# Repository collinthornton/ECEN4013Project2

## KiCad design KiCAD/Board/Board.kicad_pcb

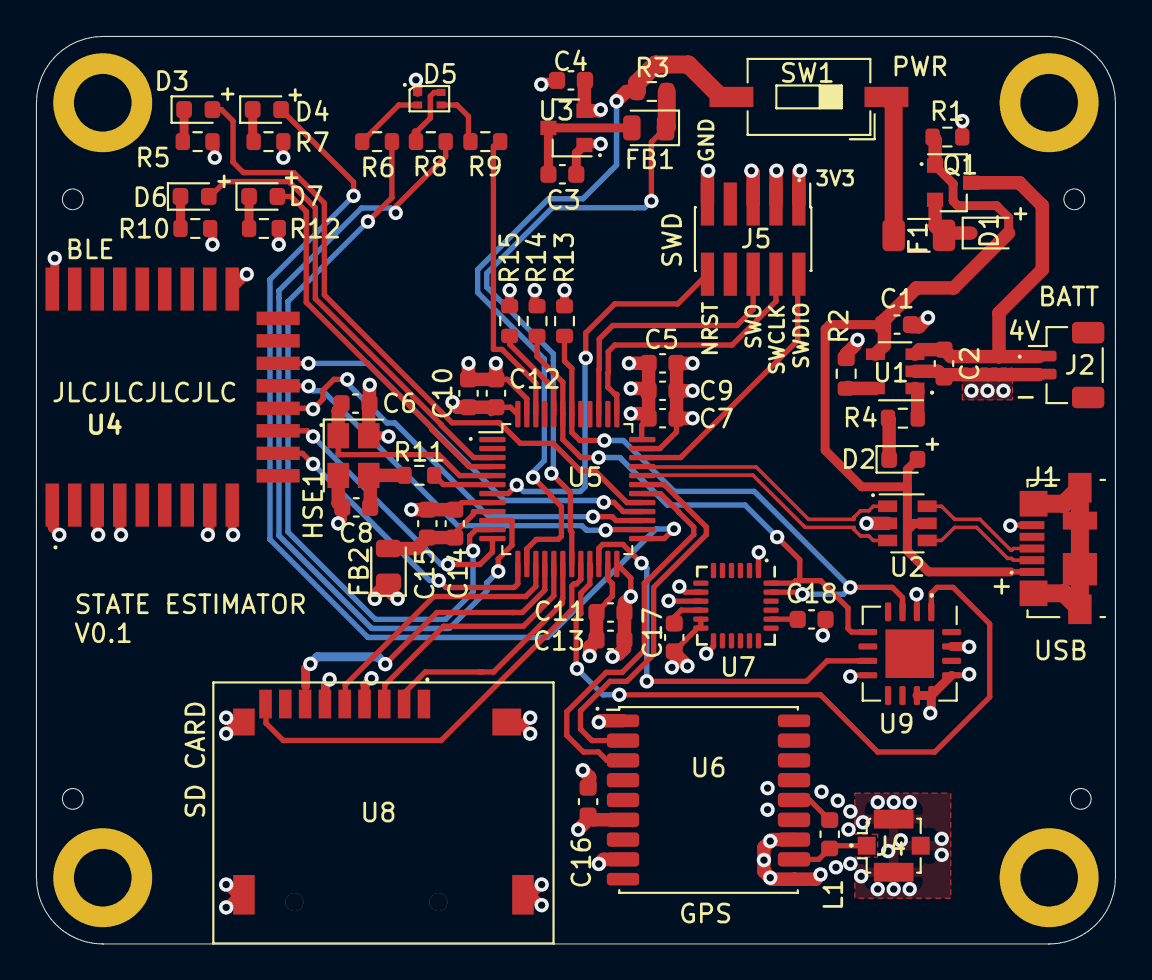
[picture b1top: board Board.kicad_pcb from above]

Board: 4 copper layers, 59.9 x 50.4 mm, 64 parts (0 on the bottom side), 59 nets.

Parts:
C1, C2: 4.7uF; C_0603_1608Metric
C3, C4: 1u; C_0603_1608Metric
C5, C16: 10u; C_0603_1608Metric
C6, C8: 14pF; C_0603_1608Metric
C7, C9, C10, C11, C12, C13, C14: 100n; C_0603_1608Metric
C15: 10n; C_0603_1608Metric
C17: 0.1u; C_0603_1608Metric
C18: 2.2n; C_0603_1608Metric
D1: D_Schottky; D_SOD-323
D2: CHARGE_LED_R; LED_0603_1608Metric
D3: GPS_STATUS; LED_0603_1608Metric
D4: SD_ACT; LED_0603_1608Metric
D5: BATT_STAT; APHF1608LSEEQBDZGKC
D6: USB_ACT; LED_0603_1608Metric
D7: BLE_CON; LED_0603_1608Metric
F1: 500mA; Fuse_1206_3216Metric
FB1, FB2: 100 @ 100 MHz; D_0805_2012Metric
H1, H2, H3, H4: MountingHole_Pad; MountingHole_3.2mm_M3_ISO14580_Pad
HSE1: 24MHz; Crystal_SMD_3225-4Pin_3.2x2.5mm
J1: USB_OTG; USB_Micro-B_Molex_47346-0001
J2: JST_BATT; JST_SH_BM02B-SRSS-TB_1x02-1MP_P1.00mm_Vertical
J4: Conn_Coaxial; U.FL_Molex_MCRF_73412-0110_Vertical
J5: Conn_02x05_Odd_Even; PinHeader_2x05_P1.27mm_Vertical_SMD
L1: 27nH; L_0603_1608Metric
Q1: PWR_PMOS; SOT-23
R1, R15: 10k; R_0603_1608Metric
R2: 5k; R_0603_1608Metric
R3: 0.4; R_0603_1608Metric
R4: 470; R_0603_1608Metric
R5, R7, R10, R12: 10; R_0603_1608Metric
R6: 50; R_0603_1608Metric
R8, R9: 34; R_0603_1608Metric
R11: 220; R_0603_1608Metric
R13, R14: 2k2; R_0603_1608Metric
SW1: ON_OFF; SW_DIP_SPSTx01_Slide_6.7x4.1mm_W8.61mm_P2.54mm_LowProfile
U1: MCP73831-2-OT; SOT-23-5
U2: USBLC6-2SC6; SOT-23-6
U3: ME6211A28M3G-N; SOT-23
U4: DS-32-BLE4.2; DL-32-BLE4.2
U5: STM32L151C8TxA; LQFP-48_7x7mm_P0.5mm
U6: ATGM336H-1N; ublox_MAX
U7: MPU-6050; InvenSense_QFN-24_4x4mm_P0.5mm
U8: Micro_SD_TF-15; MICRO_SD_TF-15
U9: MLX90393; QFN-16-1EP_5x5mm_P0.8mm_EP2.7x2.7mm

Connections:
+3.3VA: C14.1, C15.1, FB2.2, U5.9
+3V3: C4.1, C5.1, C7.1, C9.1, C10.1, C11.1, C12.1, C13.1, C16.1, D5.1, FB2.1, J5.1, R13.1, R14.1, U3.2, U4.8, U5.24, U5.36, U5.48, U6.6, U6.8, U7.8, U7.13, U8.4, U9.2, U9.8, U9.15
+5V: C1.1, D1.2, D2.2, J1.1, Q1.1, R1.1, U1.4, U2.5
BLE_EN: U4.15, U5.28
BLE_INT: U4.14, U5.26
BLE_LED_G: D7.2, U5.4
BLE_STATUS: U4.13, U5.27
BOOT0: R15.1, U5.44
GND: C1.2, C2.2, C3.2, C4.2, C5.2, C6.2, C7.2, C8.2, C9.2, C10.2, C11.2, C12.2, C13.2, C14.2, C15.2, C16.2, C17.2, C18.2, H1.1, H2.1, H3.1, H4.1, HSE1.2, HSE1.4, J1.5, J2.2, J4.2, J5.3, J5.5, J5.9, R1.2, R2.2, R5.2, R7.2, R10.2, R12.2, R15.2, U1.2, U2.2, U3.1, U4.1, U4.3, U4.4, U4.9, U4.18, U4.26, U5.8, U5.23, U5.35, U5.47, U6.1, U6.10, U6.12, U7.1, U7.9, U7.11, U7.12, U8.6, U9.11, U9.12, U9.13
GPS_LED_G: D3.2, U5.29
HSE_IN: C6.1, HSE1.1, U5.5
HSE_OUT: R11.1, U5.6
I2C1_SCL: R13.2, U5.42, U7.23, U9.3
I2C1_SDA: R14.2, U5.43, U7.24, U9.5
MLX_RDY: U5.21, U9.1
MLX_TRIG: U5.22, U9.7
NRST: J5.10, U5.7
unnamed: C3.1, FB1.2, U3.3
unnamed: C8.1, HSE1.3, R11.2
unnamed: C17.1, U7.10
unnamed: C18.1, U7.20
unnamed: D1.1, F1.2, Q1.2
unnamed: D2.1, R4.2
unnamed: D3.1, R5.1
unnamed: D4.1, R7.1
unnamed: D5.2, R6.1
unnamed: D5.3, R9.1
unnamed: D5.4, R8.1
unnamed: D6.1, R10.1
unnamed: D7.1, R12.1
unnamed: F1.1, SW1.1
unnamed: J4.1, L1.1, U6.11
unnamed: L1.2, U6.14
unnamed: R2.1, U1.5
unnamed: R4.1, U1.1
PWR_LED_B: R9.2, U5.46
PWR_LED_G: R8.2, U5.10
PWR_LED_R: R6.2, U5.11
SD_DETECT: U5.20, U8.9
SD_LED_G: D4.2, U5.25
SPI1_MISO: U5.16, U8.7
SPI1_MOSI: U5.17, U8.3
SPI1_SCK: U5.15, U8.5
SPI_CS_SD: U5.18, U8.2
SWCLK: J5.4, U5.37
SWDIO: J5.2, U5.34
SWO: J5.6, U5.39
UART1_RX: U5.31, U6.2
UART1_TX: U5.30, U6.3
UART2_RX: U4.11, U5.13
UART2_TX: U4.12, U5.12
USB_CONN_D+: J1.3, U2.6
USB_CONN_D-: J1.2, U2.4
USB_D+: U2.1, U5.33
USB_D-: U2.3, U5.32
USB_LED_G: D6.2, U5.3
V_BAT: C2.1, J2.1, Q1.3, U1.3
V_BAT_M: FB1.1, R3.1, U5.19
V_BAT_P: R3.2, SW1.2, U5.14

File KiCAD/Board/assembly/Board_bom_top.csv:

"Comment","Designator","Footprint","LCSC Part #"
"USBLC6-2SC6","U2","","C4190"
"Conn_02x05_Odd_Even","J5","","C124357"
"100 @ 100 MHz","FB2 FB1","","C1015"
"100n","C14 C7 C9 C10 C11 C12 C13","","C14663"
"10n","C15","","C57112"
"2.2n","C18","","C1604"
"0.1u","C17","","C14663"
"MPU-6050","U7","","C24112"
"2k2","R13 R14","","C4190"
"10k","R15 R1","","C25804"
"10u","C5 C16","","C19702"
"1u","C3 C4","","C15849"
"ME6211A28M3G-N","U3","",""
"250mA","F1","","C369154"
"D_Schottky","D1","","C191023"
"4.7uF","C1 C2","","C19666"
"5k","R2","","C23186"
"470","R4","","C23179"
"CHARGE_LED_R","D2","","C2286"
"MCP73831-2-OT","U1","","C424093"
"220","R11","","C22962"
"12pF","C6 C8","","C38523"
"MLX90393","U9","","C236676"
"27nH","L1","","C12100"
"Conn_Coaxial","J4","","C411563"
"DS-32-BLE4.2","U4","","C516258"
"ATGM336H-1N","U6","","C90770"
"ON_OFF","SW1","",""
"GPS_STATUS","D3","","C72043"
"SD_ACT","D4","","C72043"
"USB_ACT","D6","","C72043"
"BLE_CON","D7","","C72043"
"10","R5 R7 R10 R12","","C22859"
"BATT_STAT","D5","",""
"50","R6","","C23197"
"34","R8 R9","","C23140"
"PWR_PMOS","Q1","","C15127"
"JST_BATT","J2","","C145954"
"USB_OTG","J1","","C132560"
"0.4","R3","","C171357"
"Micro_SD_TF-15","U8","","C111196"
"STM32L151C8TxA","U5","","C9861"

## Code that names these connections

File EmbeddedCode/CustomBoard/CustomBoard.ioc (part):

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Mcu.Name=STM32L151C(6-8-B)Tx
Mcu.Package=LQFP48
Mcu.UserName=STM32L151CBTx
PA0-WKUP1.GPIOParameters=GPIO_Label
PA0-WKUP1.GPIO_Label=PWR_LED_G
PA0-WKUP1.Signal=GPIO_Output
PA1.GPIOParameters=GPIO_Label
PA1.GPIO_Label=PWR_LED_R
PA1.Signal=GPIO_Output
PA10.Mode=Asynchronous
PA10.Signal=USART1_RX
PA11.Mode=Device
PA11.Signal=USB_DM
PA12.Mode=Device
PA12.Signal=USB_DP
PA13.Mode=Trace_Asynchronous_SW
PA13.Signal=SYS_JTMS-SWDIO
PA14.Mode=Trace_Asynchronous_SW
PA14.Signal=SYS_JTCK-SWCLK
PA2.Mode=Asynchronous
PA2.Signal=USART2_TX
PA3.Mode=Asynchronous
PA3.Signal=USART2_RX
PA4.GPIOParameters=GPIO_Label
PA4.GPIO_Label=V_BAT_P
PA4.Signal=SharedAnalog_PA4
PA5.Mode=Full_Duplex_Master
PA5.Signal=SPI1_SCK
PA6.Mode=Full_Duplex_Master
PA6.Signal=SPI1_MISO
PA7.Mode=Full_Duplex_Master
PA7.Signal=SPI1_MOSI
PA8.GPIOParameters=GPIO_Label
PA8.GPIO_Label=GPS_LED_G
PA8.Signal=GPIO_Output
PA9.Mode=Asynchronous
PA9.Signal=USART1_TX
PB0.GPIOParameters=GPIO_Label
PB0.GPIO_Label=SPI_SD_CS
PB0.Signal=GPIO_Output
PB1.GPIOParameters=GPIO_Label
PB1.GPIO_Label=V_BAT_M
PB1.Signal=SharedAnalog_PB1
PB10.GPIOParameters=GPIO_Label
PB10.GPIO_Label=MLX_RDY
PB10.Signal=GPIO_Input
PB11.GPIOParameters=GPIO_Label
PB11.GPIO_Label=MLX_TRIG
PB11.Signal=GPIO_Output
PB12.GPIOParameters=GPIO_Label
PB12.GPIO_Label=SD_LED_G
PB12.Signal=GPIO_Output
PB13.GPIOParameters=GPIO_Label
PB13.GPIO_Label=BLE_INT
PB13.Signal=GPIO_Input
PB14.GPIOParameters=GPIO_Label
PB14.GPIO_Label=BLE_STATUS
PB14.Signal=GPIO_Output
PB15.GPIOParameters=GPIO_Label
PB15.GPIO_Label=BLE_EN
PB15.Signal=GPIO_Output
PB2.GPIOParameters=GPIO_PuPd,GPIO_Label
PB2.GPIO_Label=SD_DETECT
PB2.GPIO_PuPd=GPIO_PULLUP
PB2.Signal=GPIO_Input
PB3.Mode=Trace_Asynchronous_SW
PB3.Signal=SYS_JTDO-TRACESWO
PB6.Mode=I2C
PB6.Signal=I2C1_SCL
PB7.Mode=I2C
PB7.Signal=I2C1_SDA
PB9.GPIOParameters=GPIO_Label
PB9.GPIO_Label=PWR_LED_B
PB9.Signal=GPIO_Output
PC14-OSC32_IN.GPIOParameters=GPIO_Label
PC14-OSC32_IN.GPIO_Label=USB_LED_G
PC14-OSC32_IN.Signal=GPIO_Output
PC15-OSC32_OUT.GPIOParameters=GPIO_Label
PC15-OSC32_OUT.GPIO_Label=BLE_LED_G
PC15-OSC32_OUT.Signal=GPIO_Output
PH0-OSC_IN.Mode=HSE-External-Oscillator
PH0-OSC_IN.Signal=RCC_OSC_IN
PH1-OSC_OUT.Mode=HSE-External-Oscillator
PH1-OSC_OUT.Signal=RCC_OSC_OUT
RCC.HSE_VALUE=24000000
RCC.SYSCLKFreq_VALUE=16000000
RCC.SYSCLKSource=RCC_SYSCLKSOURCE_HSI
board=custom

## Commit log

2021-10-08 test
2021-10-08 removed test files
2021-10-25 major update. schematic near complete. began working on backup code
2021-10-26 initialized backup project code
2021-10-26 testing for nick
2021-10-26 Update hello.txt
    testing git with collin
2021-10-26 removing extraneous files
2021-10-26 nick-?
    I just opened the main file from my desktop and built it to confirm that I could. didnt even save anything but apparently that equates to 21 changed files.
2021-10-28 submitted board to JLCPCB
2021-11-04 finished backup board startup backup code
2021-11-04 absolutely no reason for this to be here
2021-11-04 added i2c
2021-11-04 another useless change
2021-11-04 began working on uart
2021-11-04 update uart class
2021-11-04 updated uart class
2021-11-05 updates to uart
2021-11-05 uart working well
2021-11-05 prep for i2c gyro testing
2021-11-05 bluetooth and usb working asynchronously. note that usb protocol will need to be implemented on real board
2021-11-05 commit before going to campus
2021-11-05 Revert "commit before going to campus"
    This reverts commit d158be4715ea4f703d0eeb99757ec2792cc4f039.
2021-11-05 github is dumb
2021-11-05 go back to prep commit?
2021-11-05 this is a mess
2021-11-05 reverting to collins uart since that should still work
2021-11-05 trying to get this to work
2021-11-09 began developing code for custom board
2021-11-09 working on uart
2021-11-11 gps working. mpu6050 responding, but bad values. ble responding to at commands, not connecting to wireless
2021-11-16 backup plan working splendidly. customboard needs touching up w/ sd card and mpu6050, but working pretty well.
2021-12-07 final push
2021-12-07 removed extra code and added comments
2021-12-07 final touchups
2021-12-09 replaced board sch with the backup-sh
